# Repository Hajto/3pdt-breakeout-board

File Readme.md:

# 3PDT Switch Breakout Board

A simple and clean breakout board for 3PDT (3 Pole Double Throw) switches, designed for guitar effects pedals and audio applications.

## Overview

This breakout board provides a convenient way to integrate a 3PDT switch into your guitar effects pedal projects. The board features clearly labeled connection points and is designed for easy soldering and integration.

## Connections

The breakout board provides the following connection points:

- **BIN** - Board In (input from previous stage)
- **BOUT** - Board Out (output to next stage) 
- **IN** - Guitar In (input from guitar)
- **OUT** - Guitar Signal Out (output to amplifier)
- **LED** - LED connection for status indication
- **GND** - Ground connection

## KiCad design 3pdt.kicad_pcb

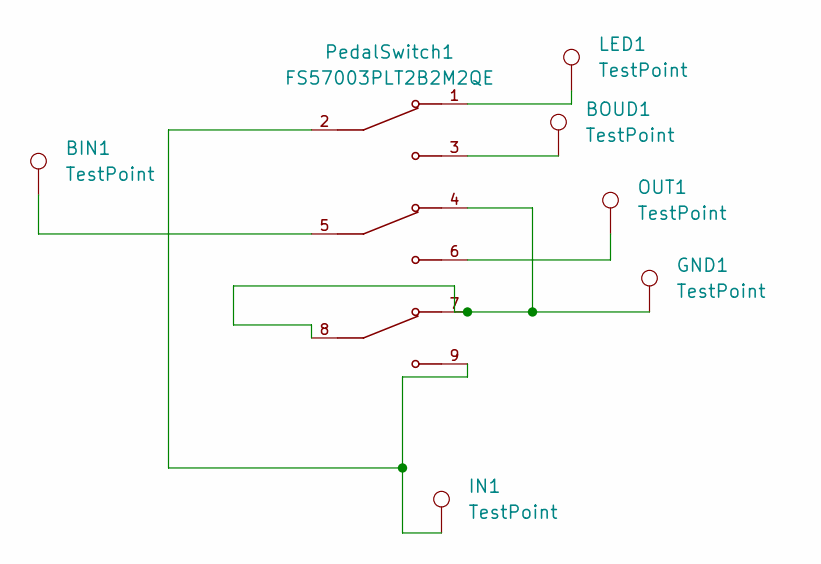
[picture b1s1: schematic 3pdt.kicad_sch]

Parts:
BIN1: TestPoint; TestPoint_THTPad_1.5x1.5mm_Drill0.7mm
BOUD1: TestPoint; TestPoint_THTPad_1.5x1.5mm_Drill0.7mm
GND1: TestPoint; TestPoint_THTPad_1.5x1.5mm_Drill0.7mm
IN1: TestPoint; TestPoint_THTPad_1.5x1.5mm_Drill0.7mm
LED1: TestPoint; TestPoint_THTPad_1.5x1.5mm_Drill0.7mm
OUT1: TestPoint; TestPoint_THTPad_1.5x1.5mm_Drill0.7mm
PedalSwitch1: FS57003PLT2B2M2QE; SW_FS57003PLT2B2M2QE; PARTREV 4.2.2018

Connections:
unnamed: BIN1.1, PedalSwitch1.5
unnamed: BOUD1.1, PedalSwitch1.3
unnamed: GND1.1, PedalSwitch1.4, PedalSwitch1.7, PedalSwitch1.8
unnamed: IN1.1, PedalSwitch1.2, PedalSwitch1.9
unnamed: LED1.1, PedalSwitch1.1
unnamed: OUT1.1, PedalSwitch1.6

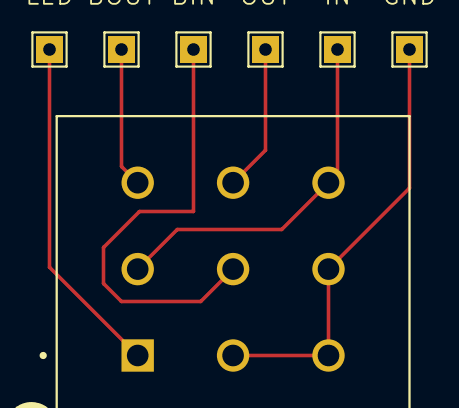
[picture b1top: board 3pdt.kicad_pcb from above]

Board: 2 copper layers, 7 parts (0 on the bottom side), 6 nets.

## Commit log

2025-09-20 Init
2025-09-20 Added README.
